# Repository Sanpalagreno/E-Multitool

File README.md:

# E-Multitool

[BOM.md](https://github.com/user-attachments/files/33780918/BOM.md)
# Bill of Materials

| Item | What it's for | Qty | Supplier | Cost/item | Total Cost |
|---|---|---|---|---|---|
| TCS34725 colour sensor (7 pins with white LED) | Reads the colour of whatever it's pointed at | 1 | AliExpress | $2.50 | $2.50 |
| GY-BME280-3.3 air sensor | Measures air pressure, temperature and humidity | 1 | AliExpress | $3.50 | $3.50 |
| TP4056 USB-C charger with DW01 protection | Charges the battery and protects it from over-discharge | 1 | AliExpress | $1.53 | $1.53 |
| TZT 650nm 5mW 6mm laser dot module | Shows where the tool is pointing | 1 | AliExpress | $0.32 | $0.32 |
| Passive piezo buzzer 3.3V | Beeps when a measurement is done | 1 | AliExpress | $0.50 | $0.50 |
| NPN transistor TO-92 (S8050 or 2N3904) | Switches the laser and the buzzer on and off | 2 | AliExpress | $0.50 | $1.00 |
| Schottky diode 1N5819 DO-41 | Stops USB power from pushing back into the battery | 1 | AliExpress | $0.50 | $0.50 |
| Resistor bags 0805 (10k, 1k, 100k, 4.7k) | Screen reset, transistor bases, battery level reading, I2C pull-ups | 4 | AliExpress | $0.40 | $1.60 |
| Capacitor bags 0805 25V (1uF, 100nF) | Screen reset and a steady battery reading | 2 | AliExpress | $0.45 | $0.90 |
| Female pin header 2.54mm 8 pins | Lets the screen plug into the board | 1 | AliExpress | $0.50 | $0.50 |
| Estimated total shipping | | 1 | | $18.60 | $18.60 |
| **Total** | | | | | **$31.45** |

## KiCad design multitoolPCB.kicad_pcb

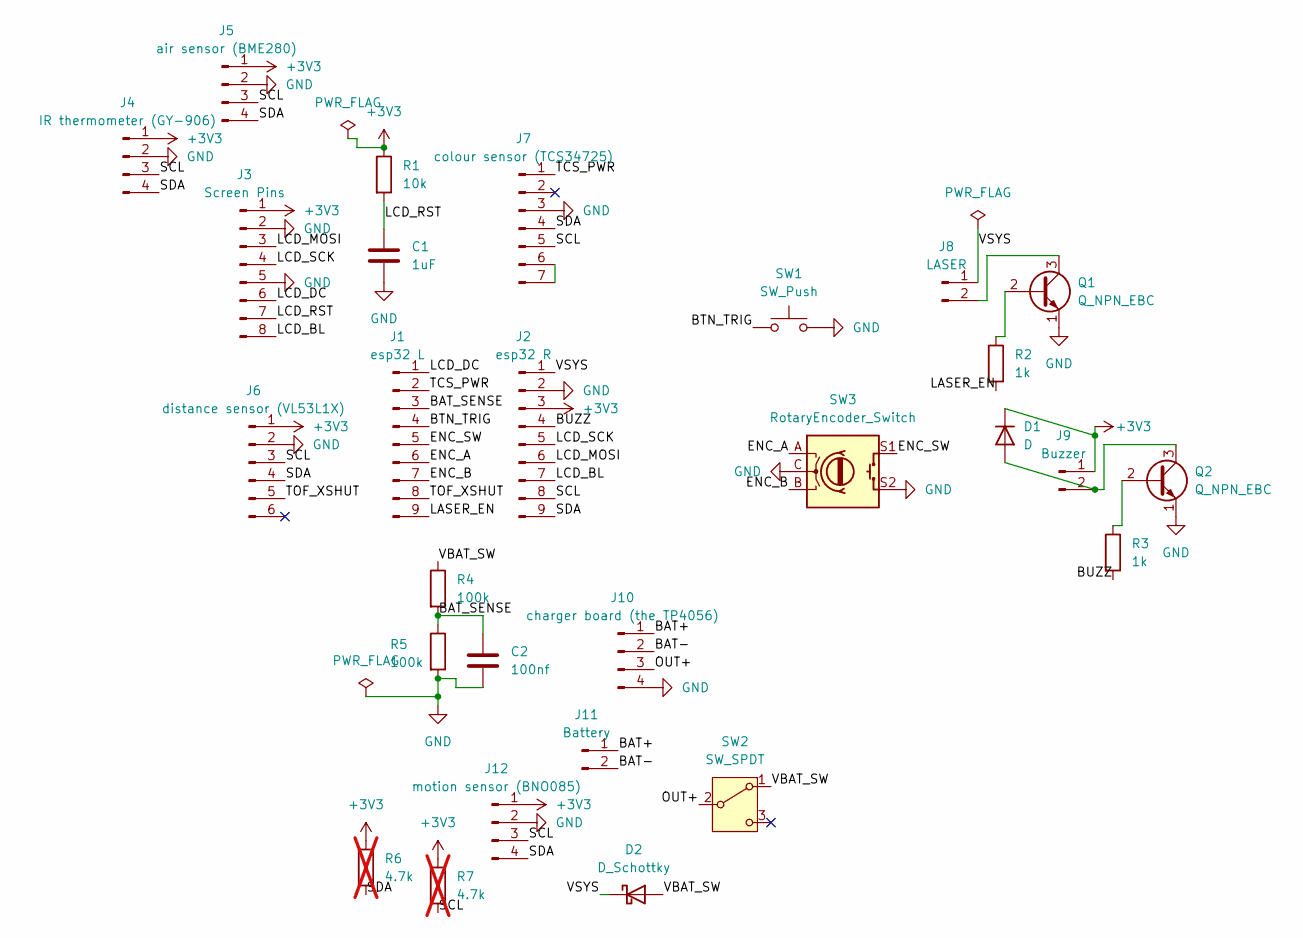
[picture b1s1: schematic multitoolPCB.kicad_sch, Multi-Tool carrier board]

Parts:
C1: 1uF; C_0805_2012Metric
C2: 100nf; C_0805_2012Metric
D1: D; D_DO-35_SOD27_P7.62mm_Horizontal
D2: D_Schottky; D_DO-41_SOD81_P10.16mm_Horizontal
J1: esp32 L; PinHeader_1x09_P2.54mm_Vertical
J2: esp32 R; PinHeader_1x09_P2.54mm_Vertical
J3: Screen Pins; PinHeader_1x08_P2.54mm_Vertical
J4: IR thermometer (GY-906); PinHeader_1x04_P2.54mm_Horizontal
J5: air sensor (BME280); PinHeader_1x04_P2.54mm_Vertical
J6: distance sensor (VL53L1X); PinHeader_1x06_P2.54mm_Horizontal
J7: colour sensor (TCS34725); PinHeader_1x07_P2.54mm_Horizontal
J8: LASER; PinHeader_1x02_P2.54mm_Vertical
J9: Buzzer; PinHeader_1x02_P2.54mm_Vertical
J10: charger board (the TP4056); PinHeader_1x04_P2.54mm_Vertical
J11: Battery; PinHeader_1x02_P2.54mm_Vertical
J12: motion sensor (BNO085); PinHeader_1x04_P2.54mm_Vertical
Q1, Q2: Q_NPN_EBC; TO-92_Inline
R1: 10k; R_0805_2012Metric
R2, R3: 1k; R_0805_2012Metric
R4, R5: 100k; R_0805_2012Metric
R6, R7: 4.7k; R_0805_2012Metric; not fitted
SW1: SW_Push; SW_PUSH_6mm
SW2: SW_SPDT; PinHeader_1x03_P2.54mm_Vertical
SW3: RotaryEncoder_Switch; RotaryEncoder_Alps_EC11E-Switch_Vertical_H20mm

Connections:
+3V3: D1.1 (K), J2.3, J3.1, J4.1, J5.1, J6.1, J9.1, J12.1, R1.1, R6.1, R7.1
/BAT+: J10.1, J11.1
/BAT-: J10.2, J11.2
/BAT_SENSE: C2.1, J1.3, R4.2, R5.1
/BTN_TRIG: J1.4, SW1.1
/BUZZ: J2.4, R3.2
/ENC_A: J1.6, SW3.A
/ENC_B: J1.7, SW3.B
/ENC_SW: J1.5, SW3.S1
/LASER_EN: J1.9, R2.2
/LCD_BL: J2.7, J3.8
/LCD_DC: J1.1, J3.6
/LCD_MOSI: J2.6, J3.3
/LCD_RST: C1.1, J3.7, R1.2
/LCD_SCK: J2.5, J3.4
/OUT+: J10.3, SW2.2 (B)
/SCL: J2.8, J4.3, J5.3, J6.3, J7.5, J12.3, R7.2
/SDA: J2.9, J4.4, J5.4, J6.4, J7.4, J12.4, R6.2
/TCS_PWR: J1.2, J7.1
/TOF_XSHUT: J1.8, J6.5
/VBAT_SW: D2.2 (A), R4.1, SW2.1 (A)
/VSYS: D2.1 (K), J2.1, J8.1
GND: C1.2, C2.2, J2.2, J3.2, J3.5, J4.2, J5.2, J6.2, J7.3, J10.4, J12.2, Q1.1 (E), Q2.1 (E), R5.2, SW1.2, SW3.C, SW3.S2
unnamed: D1.2 (A), J9.2, Q2.3 (C)
unnamed: J7.6, J7.7
unnamed: J8.2, Q1.3 (C)
unnamed: Q1.2 (B), R2.1
unnamed: Q2.2 (B), R3.1

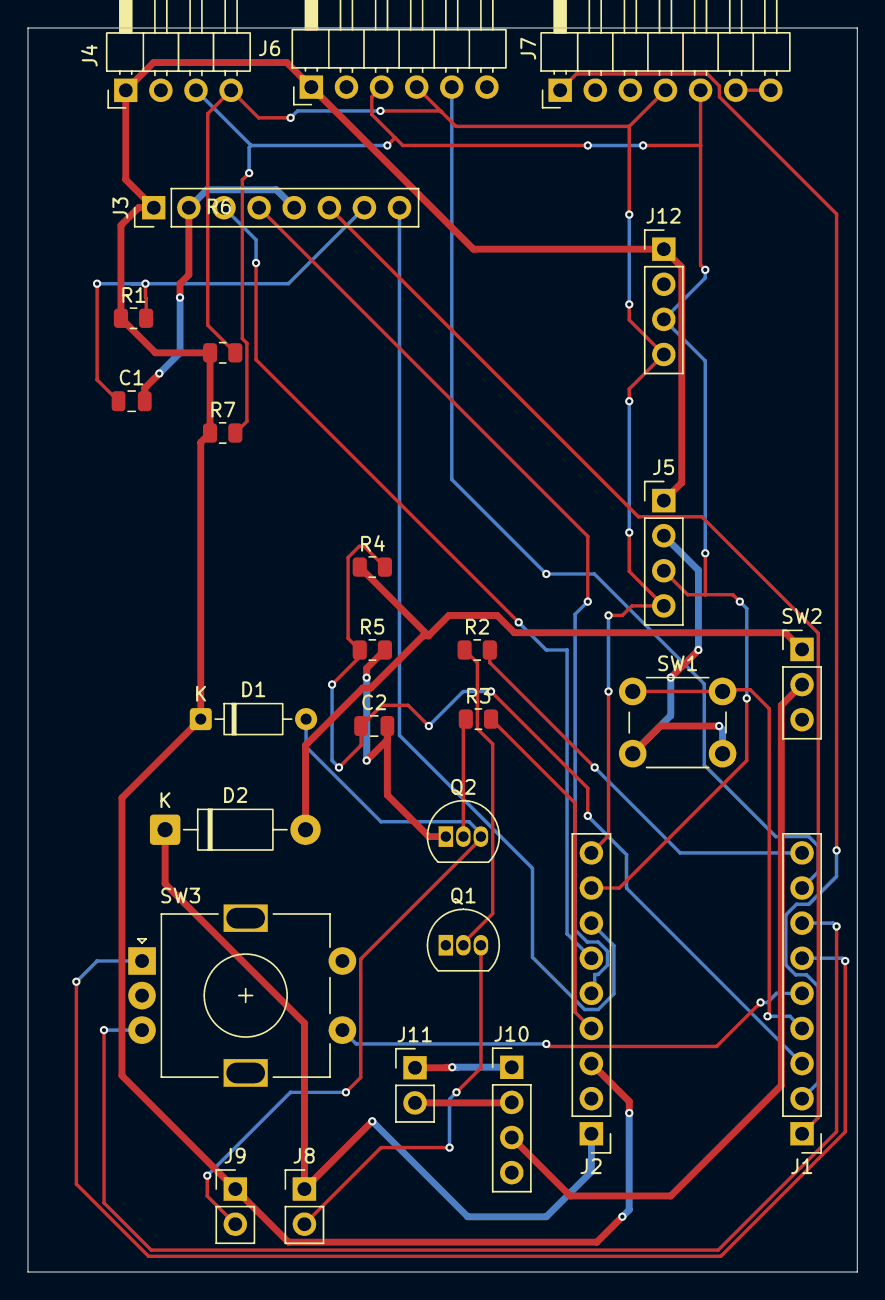
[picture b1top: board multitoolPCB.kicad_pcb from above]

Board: 2 copper layers, 60.0 x 90.0 mm, 28 parts (0 on the bottom side), 28 nets.
